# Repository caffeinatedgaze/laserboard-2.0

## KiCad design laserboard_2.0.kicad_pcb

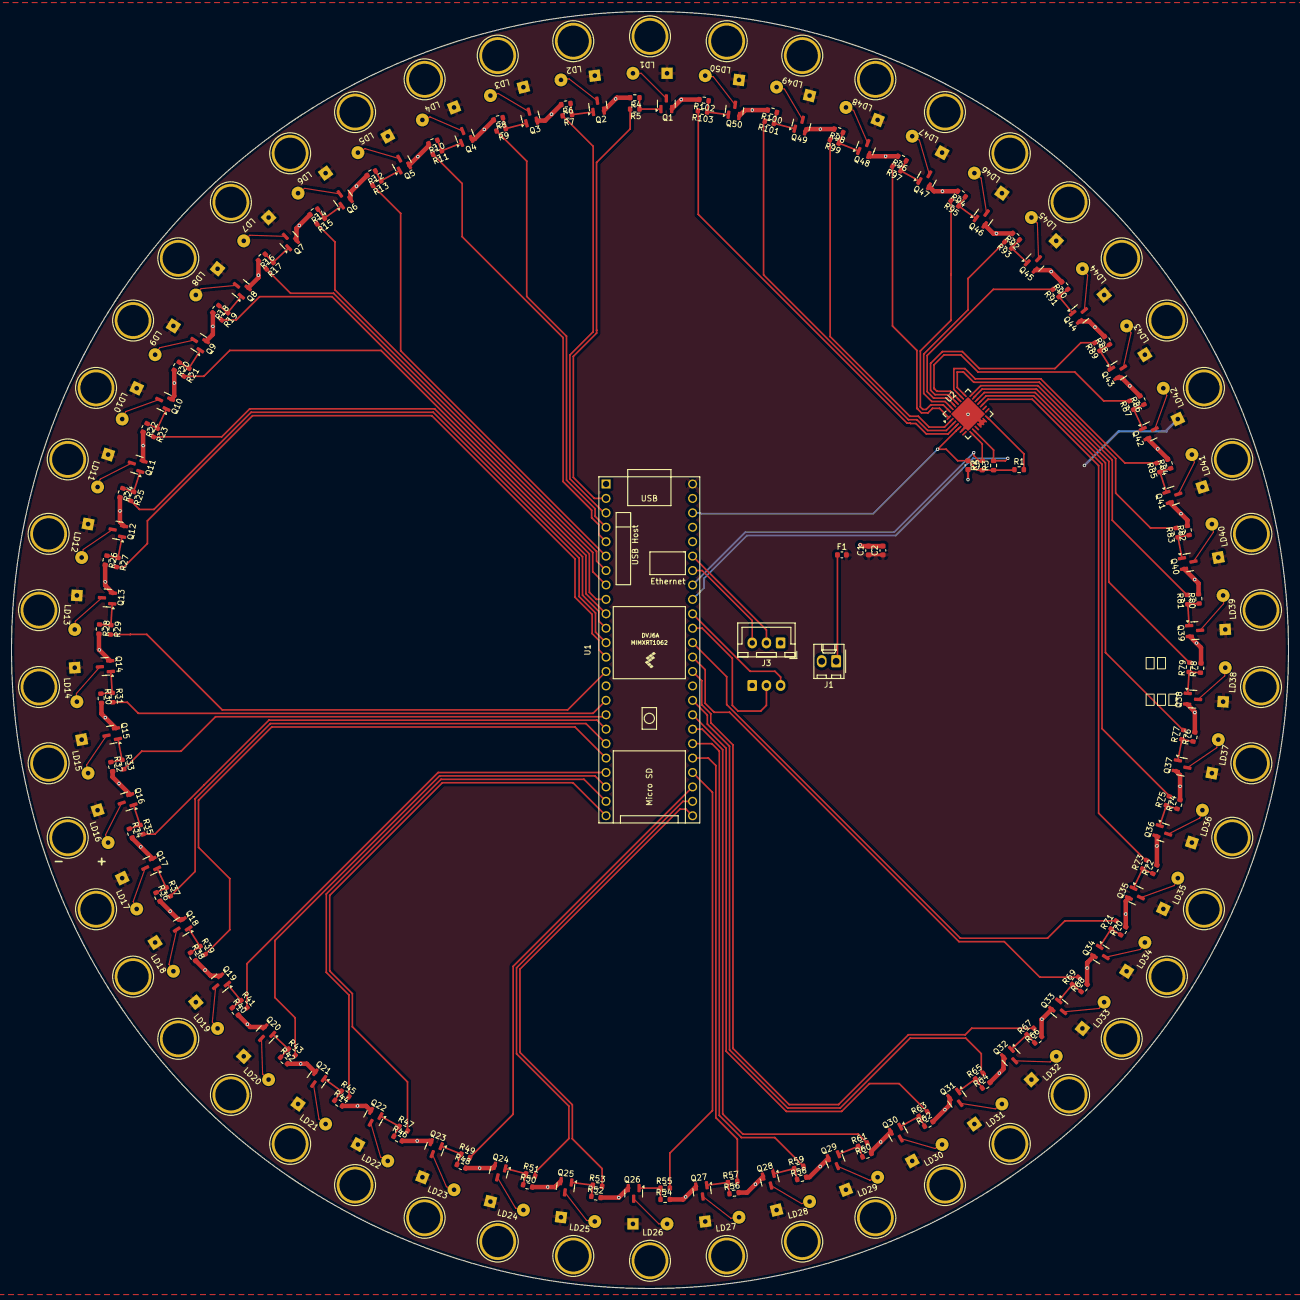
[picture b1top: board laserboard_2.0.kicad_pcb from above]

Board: 2 copper layers, 224.9 x 224.9 mm, 212 parts (1 on the bottom side), 161 nets.

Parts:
C1: 10uF; C_0603_1608Metric
C2: 0.1uF; C_0603_1608Metric
C5: 0.1; C_0603_1608Metric
F1: Fuse; Fuse_0603_1608Metric
J1: 5v; Molex_KK-254_AE-6410-02A_1x02_P2.54mm_Vertical
J3: Serial Com; JST_XH_B3B-XH-A_1x03_P2.50mm_Vertical
J4: Serial Com to rasberry; JST_XH_B3B-XH-A_1x03_P2.50mm_Vertical
LD1, LD2, LD3, LD4, LD5, LD6, LD7, LD8, LD9, LD10, LD11, LD12, LD13, LD14, LD15, LD16, LD17, LD18, LD19, LD20, LD21, LD22, LD23, LD24, LD25, LD26, LD27, LD28, LD29, LD30, LD31, LD32, LD33, LD34, LD35, LD36, LD37, LD38, LD39, LD40, LD41, LD42, LD43, LD44, LD45, LD46, LD47, LD48, LD49, LD50: D_Laser_1A3C; laser 6.0 perf
Q1, Q2, Q3, Q4, Q5, Q6, Q7, Q8, Q9, Q10, Q11, Q12, Q13, Q14, Q15, Q16, Q17, Q18, Q19, Q20, Q21, Q22, Q23, Q24, Q25, Q26, Q27, Q28, Q29, Q30, Q31, Q32, Q33, Q34, Q35, Q36, Q37, Q38, Q39, Q40, Q41, Q42, Q43, Q44, Q45, Q46, Q47, Q48, Q49, Q50: IRLML6401; SOT-23
R1, R2, R3, R4, R6, R8, R10, R12, R14, R16, R18, R20, R22, R24, R26, R28, R30, R32, R34, R36, R38, R40, R42, R44, R46, R48, R50, R52, R54, R56, R58, R60, R62, R64, R66, R68, R70, R72, R74, R76, R78, R80, R82, R84, R86, R88, R90, R92, R94, R96, R98, R100, R102: 10k; R_0603_1608Metric
R5, R7, R9, R11, R13, R15, R17, R19, R21, R23, R25, R27, R29, R31, R33, R35, R37, R39, R41, R43, R45, R47, R49, R51, R53, R55, R57, R59, R61, R63, R65, R67, R69, R71, R73, R75, R77, R79, R81, R83, R85, R87, R89, R91, R93, R95, R97, R99, R101, R103: 220; R_0603_1608Metric
U1: Teensy4.1; Teensy41
U2: MCP23017_ML; QFN-28-1EP_6x6mm_P0.65mm_EP4.25x4.25mm

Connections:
/3v: C5.1, R1.1, R2.1, R3.1, U1.46 (3V3), U2.5 (VDD)
/A1: R5.1, U1.2 (0_RX1_CRX2_CS1)
/A2: R7.1, U1.3 (1_TX1_CTX2_MISO1)
/A3: R9.1, U1.4 (2_OUT2)
/A4: R11.1, U1.5 (3_LRCLK2)
/A5: R13.1, U1.6 (4_BCLK2)
/A6: R15.1, U1.7 (5_IN2)
/A7: R17.1, U1.8 (6_OUT1D)
/A8: R19.1, U1.9 (7_RX2_OUT1A)
/A9: R21.1, U1.10 (8_TX2_IN1)
/A10: R23.1, U1.11 (9_OUT1C)
/A11: R25.1, U1.12 (10_CS_MQSR)
/A12: R27.1, U1.13 (11_MOSI_CTX1)
/A13: R29.1, U1.14 (12_MISO_MQSL)
/A14: R31.1, U1.16 (24_A10_TX6_SCL2)
/A15: R33.1, U1.17 (25_A11_RX6_SDA2)
/A16: R35.1, U1.18 (26_A12_MOSI1)
/A17: R37.1, U1.19 (27_A13_SCK1)
/A18: R39.1, U1.20 (28_RX7)
/A19: R41.1, U1.21 (29_TX7)
/A20: R43.1, U1.22 (30_CRX3)
/A21: R45.1, U1.23 (31_CTX3)
/A22: R47.1, U1.24 (32_OUT1B)
/A23: R49.1, U1.27 (35_TX8)
/A24: R51.1, U1.26 (34_RX8)
/A25: R53.1, U1.25 (33_MCLK2)
/A26: R55.1, U1.28 (36_CS)
/A27: R57.1, U1.29 (37_CS)
/A28: R59.1, U1.30 (38_CS1_IN1)
/A29: R61.1, U1.31 (39_MISO1_OUT1A)
/A30: R63.1, U1.32 (40_A16)
/A31: R65.1, U1.33 (41_A17)
/A32: R67.1, U1.35 (13_SCK_LED)
/A33: R69.1, U1.36 (14_A0_TX3_SPDIF_OUT)
/A34: R71.1, U1.37 (15_A1_RX3_SPDIF_IN)
/A35: R73.1, U2.17 (GPA0)
/A36: R75.1, U2.18 (GPA1)
/A37: R77.1, U2.19 (GPA2)
/A38: R79.1, U2.20 (GPA3)
/A39: R81.1, U2.21 (GPA4)
/A40: R83.1, U2.22 (GPA5)
/A41: R85.1, U2.23 (GPA6)
/A42: R87.1, U2.24 (GPA7)
/A43: R89.1, U2.25 (GPB0)
/A44: R91.1, U2.26 (GPB1)
/A45: R93.1, U2.27 (GPB2)
/A46: R95.1, U2.28 (GPB3)
/A47: R97.1, U2.1 (GPB4)
/A48: R99.1, U2.2 (GPB5)
/A49: R101.1, U2.3 (GPB6)
/A50: R103.1, U2.4 (GPB7)
/P_RX: J4.3, U1.39 (17_A3_TX4_SDA1)
/P_TX: J4.2, U1.38 (16_A2_RX4_SCL1)
/RX: J3.2, U1.43 (21_A7_RX5_BCLK1)
/SCL: R2.2, U1.41 (19_A5_SCL), U2.8 (SCK)
/SDA: R3.2, U1.40 (18_A4_SDA), U2.9 (SDA)
/TX: J3.3, U1.42 (20_A6_TX5_LRCLK1)
GND: C1.2, C2.2, C5.2, J1.2, J3.1, J4.1, Q1.2 (S), Q2.2 (S), Q3.2 (S), Q4.2 (S), Q5.2 (S), Q6.2 (S), Q7.2 (S), Q8.2 (S), Q9.2 (S), Q10.2 (S), Q11.2 (S), Q12.2 (S), Q13.2 (S), Q14.2 (S), Q15.2 (S), Q16.2 (S), Q17.2 (S), Q18.2 (S), Q19.2 (S), Q20.2 (S), Q21.2 (S), Q22.2 (S), Q23.2 (S), Q24.2 (S), Q25.2 (S), Q26.2 (S), Q27.2 (S), Q28.2 (S), Q29.2 (S), Q30.2 (S), Q31.2 (S), Q32.2 (S), Q33.2 (S), Q34.2 (S), Q35.2 (S), Q36.2 (S), Q37.2 (S), Q38.2 (S), Q39.2 (S), Q40.2 (S), Q41.2 (S), Q42.2 (S), Q43.2 (S), Q44.2 (S), Q45.2 (S), Q46.2 (S), Q47.2 (S), Q48.2 (S), Q49.2 (S), Q50.2 (S), R4.2, R6.2, R8.2, R10.2, R12.2, R14.2, R16.2, R18.2, R20.2, R22.2, R24.2, R26.2, R28.2, R30.2, R32.2, R34.2, R36.2, R38.2, R40.2, R42.2, R44.2, R46.2, R48.2, R50.2, R52.2, R54.2, R56.2, R58.2, R60.2, R62.2, R64.2, R66.2, R68.2, R70.2, R72.2, R74.2, R76.2, R78.2, R80.2, R82.2, R84.2, R86.2, R88.2, R90.2, R92.2, R94.2, R96.2, R98.2, R100.2, R102.2, U1.47 (GND), U2.6 (VSS), U2.11 (A0), U2.12 (A1), U2.13 (A2), U2.29 (EP)
Laser power: C1.1, C2.1, F1.2, LD1.1 (A), LD2.1 (A), LD3.1 (A), LD4.1 (A), LD5.1 (A), LD6.1 (A), LD7.1 (A), LD8.1 (A), LD9.1 (A), LD10.1 (A), LD11.1 (A), LD12.1 (A), LD13.1 (A), LD14.1 (A), LD15.1 (A), LD16.1 (A), LD17.1 (A), LD18.1 (A), LD19.1 (A), LD20.1 (A), LD21.1 (A), LD22.1 (A), LD23.1 (A), LD24.1 (A), LD25.1 (A), LD26.1 (A), LD27.1 (A), LD28.1 (A), LD29.1 (A), LD30.1 (A), LD31.1 (A), LD32.1 (A), LD33.1 (A), LD34.1 (A), LD35.1 (A), LD36.1 (A), LD37.1 (A), LD38.1 (A), LD39.1 (A), LD40.1 (A), LD41.1 (A), LD42.1 (A), LD43.1 (A), LD44.1 (A), LD45.1 (A), LD46.1 (A), LD47.1 (A), LD48.1 (A), LD49.1 (A), LD50.1 (A), U1.48 (VIN)
unnamed: F1.1, J1.1
unnamed: LD1.2 (K), Q1.3 (D)
unnamed: LD2.2 (K), Q2.3 (D)
unnamed: LD3.2 (K), Q3.3 (D)
unnamed: LD4.2 (K), Q4.3 (D)
unnamed: LD5.2 (K), Q5.3 (D)
unnamed: LD6.2 (K), Q6.3 (D)
unnamed: LD7.2 (K), Q7.3 (D)
unnamed: LD8.2 (K), Q8.3 (D)
unnamed: LD9.2 (K), Q9.3 (D)
unnamed: LD10.2 (K), Q10.3 (D)
unnamed: LD11.2 (K), Q11.3 (D)
unnamed: LD12.2 (K), Q12.3 (D)
unnamed: LD13.2 (K), Q13.3 (D)
unnamed: LD14.2 (K), Q14.3 (D)
unnamed: LD15.2 (K), Q15.3 (D)
unnamed: LD16.2 (K), Q16.3 (D)
unnamed: LD17.2 (K), Q17.3 (D)
unnamed: LD18.2 (K), Q18.3 (D)
unnamed: LD19.2 (K), Q19.3 (D)
unnamed: LD20.2 (K), Q20.3 (D)
unnamed: LD21.2 (K), Q21.3 (D)
unnamed: LD22.2 (K), Q22.3 (D)
unnamed: LD23.2 (K), Q23.3 (D)
unnamed: LD24.2 (K), Q24.3 (D)
unnamed: LD25.2 (K), Q25.3 (D)
unnamed: LD26.2 (K), Q26.3 (D)
unnamed: LD27.2 (K), Q27.3 (D)
unnamed: LD28.2 (K), Q28.3 (D)
unnamed: LD29.2 (K), Q29.3 (D)
unnamed: LD30.2 (K), Q30.3 (D)
unnamed: LD31.2 (K), Q31.3 (D)
unnamed: LD32.2 (K), Q32.3 (D)
unnamed: LD33.2 (K), Q33.3 (D)
unnamed: LD34.2 (K), Q34.3 (D)
unnamed: LD35.2 (K), Q35.3 (D)
unnamed: LD36.2 (K), Q36.3 (D)
unnamed: LD37.2 (K), Q37.3 (D)
unnamed: LD38.2 (K), Q38.3 (D)
unnamed: LD39.2 (K), Q39.3 (D)
unnamed: LD40.2 (K), Q40.3 (D)
unnamed: LD41.2 (K), Q41.3 (D)
unnamed: LD42.2 (K), Q42.3 (D)
unnamed: LD43.2 (K), Q43.3 (D)
unnamed: LD44.2 (K), Q44.3 (D)
unnamed: LD45.2 (K), Q45.3 (D)
unnamed: LD46.2 (K), Q46.3 (D)
unnamed: LD47.2 (K), Q47.3 (D)
unnamed: LD48.2 (K), Q48.3 (D)
unnamed: LD49.2 (K), Q49.3 (D)
unnamed: LD50.2 (K), Q50.3 (D)
unnamed: Q1.1 (G), R4.1, R5.2
unnamed: Q2.1 (G), R6.1, R7.2
unnamed: Q3.1 (G), R8.1, R9.2
unnamed: Q4.1 (G), R10.1, R11.2
unnamed: Q5.1 (G), R12.1, R13.2
unnamed: Q6.1 (G), R14.1, R15.2
unnamed: Q7.1 (G), R16.1, R17.2
unnamed: Q8.1 (G), R18.1, R19.2
unnamed: Q9.1 (G), R20.1, R21.2
unnamed: Q10.1 (G), R22.1, R23.2
unnamed: Q11.1 (G), R24.1, R25.2
unnamed: Q12.1 (G), R26.1, R27.2
unnamed: Q13.1 (G), R28.1, R29.2
unnamed: Q14.1 (G), R30.1, R31.2
unnamed: Q15.1 (G), R32.1, R33.2
unnamed: Q16.1 (G), R34.1, R35.2
unnamed: Q17.1 (G), R36.1, R37.2
unnamed: Q18.1 (G), R38.1, R39.2
unnamed: Q19.1 (G), R40.1, R41.2
unnamed: Q20.1 (G), R42.1, R43.2
unnamed: Q21.1 (G), R44.1, R45.2
unnamed: Q22.1 (G), R46.1, R47.2
unnamed: Q23.1 (G), R48.1, R49.2
unnamed: Q24.1 (G), R50.1, R51.2
unnamed: Q25.1 (G), R52.1, R53.2
unnamed: Q26.1 (G), R54.1, R55.2
unnamed: Q27.1 (G), R56.1, R57.2
unnamed: Q28.1 (G), R58.1, R59.2
unnamed: Q29.1 (G), R60.1, R61.2
unnamed: Q30.1 (G), R62.1, R63.2
unnamed: Q31.1 (G), R64.1, R65.2
unnamed: Q32.1 (G), R66.1, R67.2
unnamed: Q33.1 (G), R68.1, R69.2
unnamed: Q34.1 (G), R70.1, R71.2
unnamed: Q35.1 (G), R72.1, R73.2
unnamed: Q36.1 (G), R74.1, R75.2
unnamed: Q37.1 (G), R76.1, R77.2
unnamed: Q38.1 (G), R78.1, R79.2
unnamed: Q39.1 (G), R80.1, R81.2
unnamed: Q40.1 (G), R82.1, R83.2
unnamed: Q41.1 (G), R84.1, R85.2
unnamed: Q42.1 (G), R86.1, R87.2
unnamed: Q43.1 (G), R88.1, R89.2
unnamed: Q44.1 (G), R90.1, R91.2
unnamed: Q45.1 (G), R92.1, R93.2
unnamed: Q46.1 (G), R94.1, R95.2
unnamed: Q47.1 (G), R96.1, R97.2
unnamed: Q48.1 (G), R98.1, R99.2
unnamed: Q49.1 (G), R100.1, R101.2
unnamed: Q50.1 (G), R102.1, R103.2
unnamed: R1.2, U2.14 (~RESET)

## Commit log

2025-12-08 Upload files
2025-12-09 Finalize
    - Copper fills
    - Trees
    - Holes
2025-12-10 Prepare for upload
